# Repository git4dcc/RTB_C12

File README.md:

# RTB_C12

My homebrew RTB C12 Micro Booster implements a booster, DCC generator and Real-time Railcom detector. The booster is optimized for N-scale in respect to track voltage and current.

<details>
<summary>See also</summary>

- [RTB_C10 - Master](https://github.com/git4dcc/RTB_C10)
- [RTB_C11 - Power](https://github.com/git4dcc/RTB_C11)
- [RTB_C13 - Track Sensor](https://github.com/git4dcc/RTB_C13)
- [RTB_P15 - Base](https://github.com/git4dcc/RTB_P15)

</details>

<details>
<summary>User Guides</summary>

- User Guide - DE
- [User Guide - EN](https://rtb4dcc.de/rtb_user_guide_en/)

</details>

## Booster features
- **FDX**
  - FDX bus (2Mbps full duplex)
- **DCC protocol generator**
  - unlimited decoder stack depth
  - DCC bandwidth monitor
  - DCC-A protocol (incl. stretched start bit)
  - DCC-R protocol (incl. update of RTB decoder on main)
- **MDU protocol generator**
  - Zimo MDU ([Multi Decoder Update](https://github.com/ZIMO-Elektronik/MDU))
  - update of MS and MN decoder
  - can update multiple MN/MS decoder concurrently
- **DECUP protocol generator**
  - Zimo DECUP ([**Dec**oder **Up**date](https://github.com/ZIMO-Elektronik/DECUP))
  - update of MX decoder
- **Booster**
  - Software programmable output voltage (3..18V)
  - 1A continuous current (1.5A peak)
  - Current limiter
  - Short circuit detection
  - Configurable bridge dead time (170ns..3500ns)
  - DCC signal timing adjustable [micro sec granularity]
  - Railcom Cutout timing adjustable
  - Up to 500kHz fast signaling
  - Voltage and current measurement
- **Railcom Detector**
  - channel 1 / channel 2
  - detects unlimited number of decoder
  - Railcom polarity detection
  - Railcom timing capture for decoder analysis
- **Service Mode**
  - read/write DCC decoder in “service mode”
  - ACK current detector adjustable
- **Firmware update over the bus**

# Hardware
The PCB layout uses SMD footprints with 0.4mm pitch and mostly 0603 parts. Reflow soldering is recommended, but with some experience handsoldering is also possible.
Further, the PCB has been optimized for automated assembly (BOM and Position files as CSV).

## PCB
- 4-layer PCB, FR4, 1.6mm
- CPU: AVR64DB48
- H-Bridge: BD63573NUV
- Voltage: OPA521

## Kicad
[Schematic](doc/C12_schematic.pdf) | [Layout](doc/C12_layout.pdf) | [Gerber](gerber)

# Firmware
Filename structure: { **pcb** }{ **code** }{ **version** }.hex

Example: **C12F0001**.hex

|   | Description |
| --- | --- |
| **pcb** | Name of matching hardware (**C12**) |
| **code** | Type of code contained (**R**=rom, **B**=bootloader, **F**=flash, **U**=bld update, **P**=UPDI factory code) |
| **version** | Release version (**####**) |

[Firmware files](firmware)

## UPDI / Fuses
The fuse settings as well as the P-code (C12Pxxxx.hex) has to be installed by using UPDI.<br>

| Fuses Setting |
| --- |
||

# Images

# YouTube
See the C12 booster in action.<br><br>

This project is intended for hobby use only and is distributed in accordance with the Apache License 2.0 agreement.

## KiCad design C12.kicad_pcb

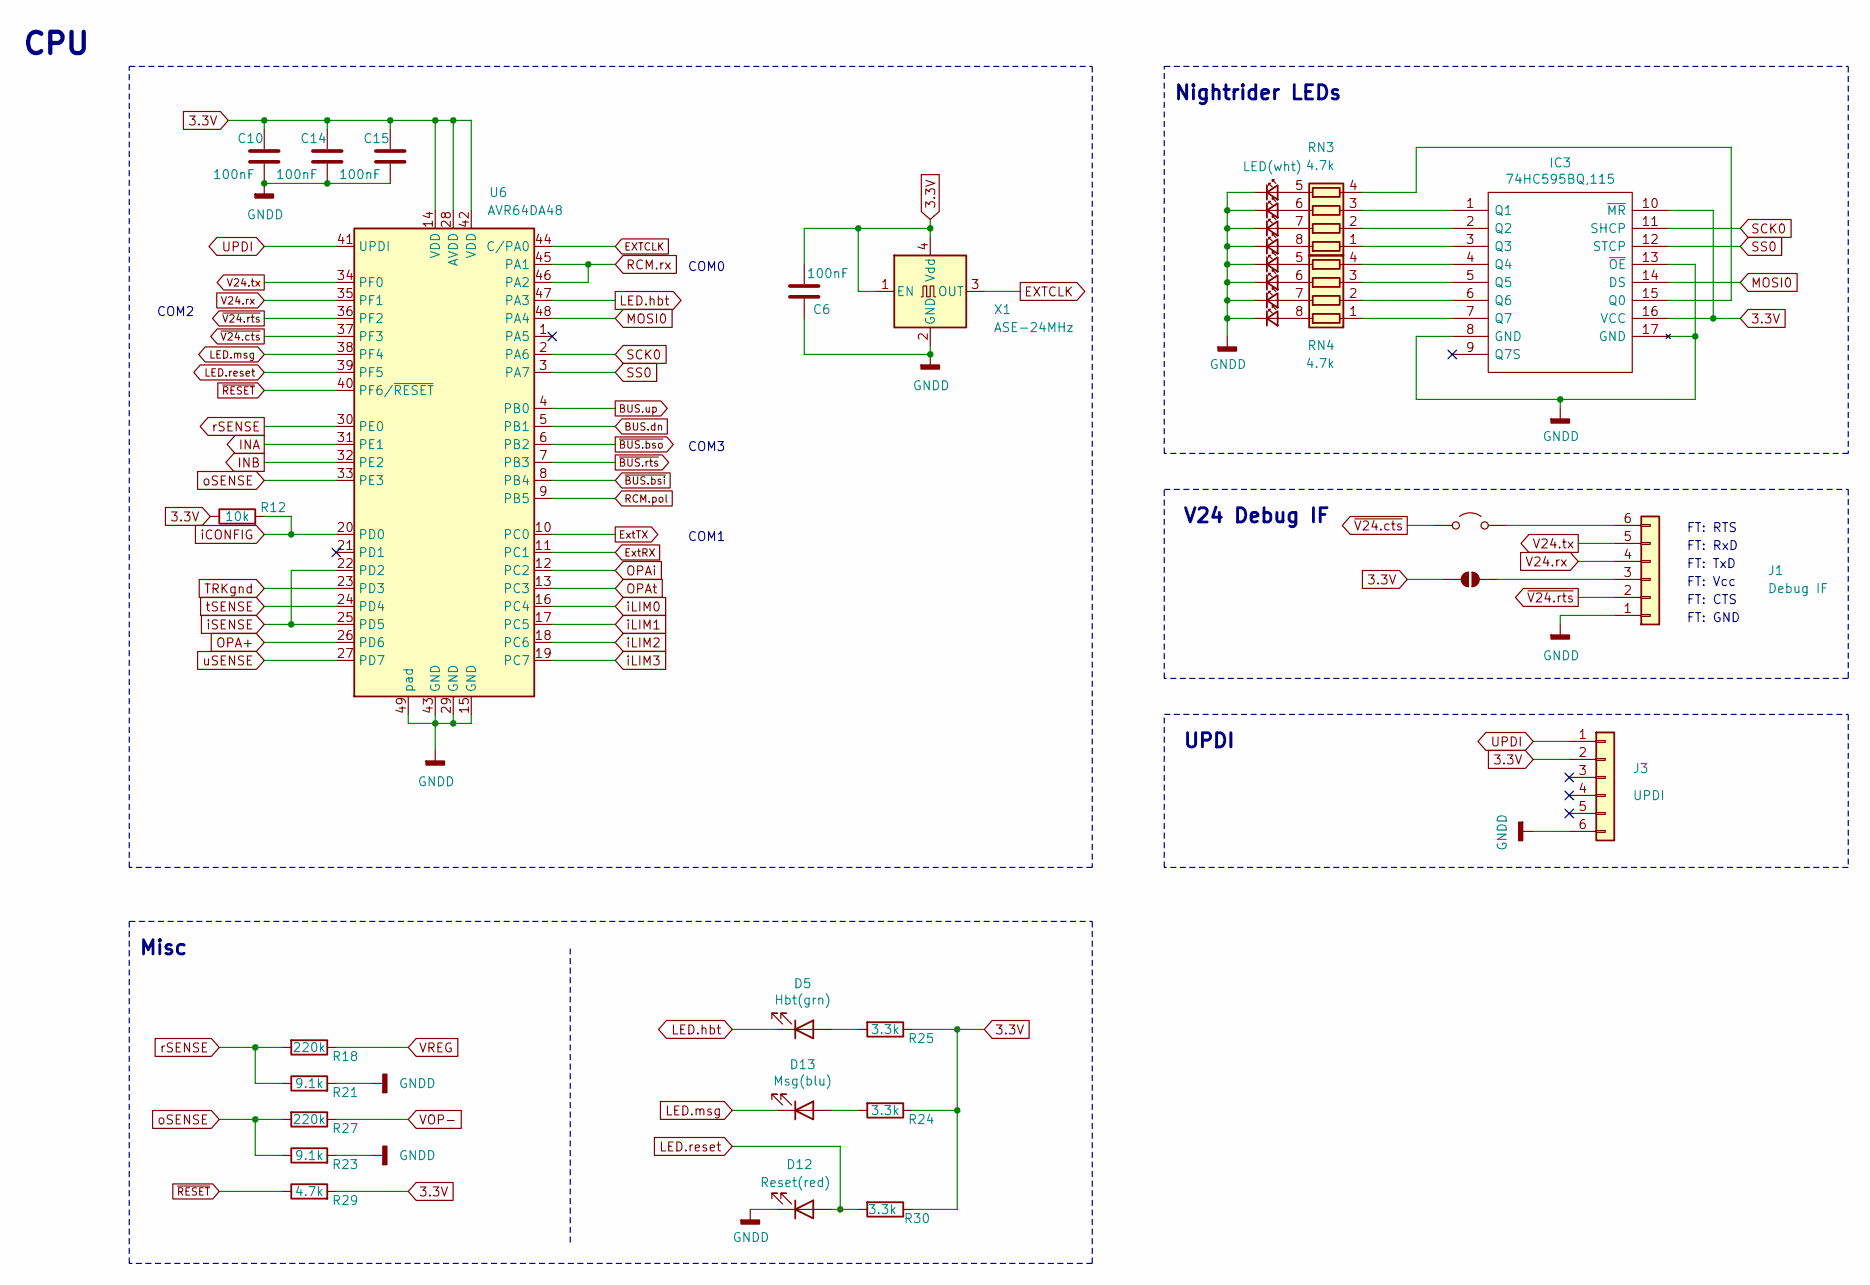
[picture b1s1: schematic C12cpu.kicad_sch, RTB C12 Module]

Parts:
C6, C10, C14, C15: 100nF; C_0402_1005Metric; LCSC Part # C307331
D5: Hbt(grn); LED_0603_1608Metric; LCSC Part # C84264
D12: Reset(red); LED_0603_1608Metric; LCSC Part # C2986060
D13: Msg(blu); LED_0603_1608Metric; LCSC Part # C434421
D14, D32, D33, D34, D35, D36, D37: LED_Small; LED_0603_1608Metric; LCSC Part # C2290
D38: LED(wht); LED_0603_1608Metric; LCSC Part # C2290
IC3: 74HC595BQ,115; DHVQFN-16-1EP_2.5x3.5mm_P0.5mm_EP1x2mm; LCSC Part # C547123
J1: Debug IF; PinHeader_1x06_P2.54mm_Vertical
J3: UPDI; PinHeader_2x03_P1.27mm_Vertical
JP1: Jumper_2_Open; PinHeader_1x02_P2.54mm_Vertical
JP2: SolderJumper_2_Open; SolderJumper-2_P1.3mm_Open_RoundedPad1.0x1.5mm
R12: 10k; R_0603_1608Metric; LCSC Part # C25804
R18, R27: 220k; R_0603_1608Metric; LCSC Part # C22961
R21, R23: 9.1k; R_0603_1608Metric; LCSC Part # C23260
R24, R25, R30: 3.3k; R_0603_1608Metric; LCSC Part # C22978
R29: 4.7k; R_0603_1608Metric; LCSC Part # C23162
RN3, RN4: 4.7k; R_Array_Convex_4x0603; LCSC Part # C1980
U6: AVR64DA48; QFN-48-1EP_6x6mm_P0.4mm_EP4.2x4.2mm; LCSC Part # C3227399
X1: ASE-24MHz; Oscillator_SMD_Abracon_ASE-4Pin_3.2x2.5mm; LCSC Part # C1987527

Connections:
3.3V: C6.1, C10.1, C14.1, C15.1, IC3.10 (~MR), IC3.16 (VCC), J3.2, JP2.1 (A), R12.1, R24.1, R25.1, R29.2, R30.1, U6.14 (VDD), U6.28 (AVDD), U6.42 (VDD), X1.1 (EN), X1.4 (Vdd); also elsewhere on the board
BUS.dn: U6.5 (PB1); also elsewhere on the board
BUS.up: U6.4 (PB0); also elsewhere on the board
EXTCLK: U6.44 (C/PA0), X1.3 (OUT)
ExtRX: U6.11 (PC1); also elsewhere on the board
ExtTX: U6.10 (PC0); also elsewhere on the board
GNDD: C6.2, C10.2, C14.2, C15.2, D12.1 (K), D14.1 (K), D32.1 (K), D33.1 (K), D34.1 (K), D35.1 (K), D36.1 (K), D37.1 (K), D38.1 (K), IC3.8 (GND), IC3.13 (~OE), IC3.17 (GND), J1.1, J3.6, R21.2, R23.2, U6.15 (GND), U6.29 (GND), U6.43 (GND), U6.49 (GND), X1.2 (GND); also elsewhere on the board
INA: U6.31 (PE1); also elsewhere on the board
INB: U6.32 (PE2); also elsewhere on the board
LED.hbt: D5.1 (K), U6.47 (PA3)
LED.msg: D13.1 (K), U6.38 (PF4)
LED.reset: D12.2 (A), R30.2, U6.39 (PF5)
MOSI0: IC3.14 (DS), U6.48 (PA4)
unnamed: D5.2 (A), R25.2
unnamed: D13.2 (A), R24.2
unnamed: D14.2 (A), RN4.8 (R1.2)
unnamed: D32.2 (A), RN4.7 (R2.2)
unnamed: D33.2 (A), RN4.6 (R3.2)
unnamed: D34.2 (A), RN4.5 (R4.2)
unnamed: D35.2 (A), RN3.8 (R1.2)
unnamed: D36.2 (A), RN3.7 (R2.2)
unnamed: D37.2 (A), RN3.6 (R3.2)
unnamed: D38.2 (A), RN3.5 (R4.2)
unnamed: IC3.15 (Q0), RN3.4 (R4.1)
unnamed: IC3.1 (Q1), RN3.3 (R3.1)
unnamed: IC3.2 (Q2), RN3.2 (R2.1)
unnamed: IC3.3 (Q3), RN3.1 (R1.1)
unnamed: IC3.4 (Q4), RN4.4 (R4.1)
unnamed: IC3.5 (Q5), RN4.3 (R3.1)
unnamed: IC3.6 (Q6), RN4.2 (R2.1)
unnamed: IC3.7 (Q7), RN4.1 (R1.1)
unnamed: J1.3, JP2.2 (B)
unnamed: J1.6, JP1.1 (A)
OPA+: U6.26 (PD6); also elsewhere on the board
OPAi: U6.12 (PC2); also elsewhere on the board
OPAt: U6.13 (PC3); also elsewhere on the board
RCM.pol: U6.9 (PB5); also elsewhere on the board
RCM.rx: U6.45 (PA1), U6.46 (PA2); also elsewhere on the board
SCK0: IC3.11 (SHCP), U6.2 (PA6)
SS0: IC3.12 (STCP), U6.3 (PA7)
TRKgnd: U6.23 (PD3); also elsewhere on the board
UPDI: J3.1, U6.41 (UPDI)
V24.rx: J1.4, U6.35 (PF1)
V24.tx: J1.5, U6.34 (PF0)
VOP-: R27.1; also elsewhere on the board
VREG: R18.1; also elsewhere on the board
iCONFIG: R12.2, U6.20 (PD0); also elsewhere on the board
iLIM0: U6.16 (PC4); also elsewhere on the board
iLIM1: U6.17 (PC5); also elsewhere on the board
iLIM2: U6.18 (PC6); also elsewhere on the board
iLIM3: U6.19 (PC7); also elsewhere on the board
iSENSE: U6.22 (PD2), U6.25 (PD5); also elsewhere on the board
oSENSE: R23.1, R27.2, U6.33 (PE3)
rSENSE: R18.2, R21.1, U6.30 (PE0)
tSENSE: U6.24 (PD4); also elsewhere on the board
uSENSE: U6.27 (PD7); also elsewhere on the board
~BUS.bsi: U6.8 (PB4); also elsewhere on the board
~BUS.bso: U6.6 (PB2); also elsewhere on the board
~BUS.rts: U6.7 (PB3); also elsewhere on the board
~RESET: R29.1, U6.40 (PF6/~RESET); also elsewhere on the board
~V24.cts: JP1.2 (B), U6.37 (PF3)
~V24.rts: J1.2, U6.36 (PF2)

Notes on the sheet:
FT: GND
Misc
COM0
COM1
UPDI
Nightrider LEDs
FT: RTS
FT: Vcc
FT: CTS
FT: RxD
COM2
COM3
FT: TxD
CPU
V24 Debug IF

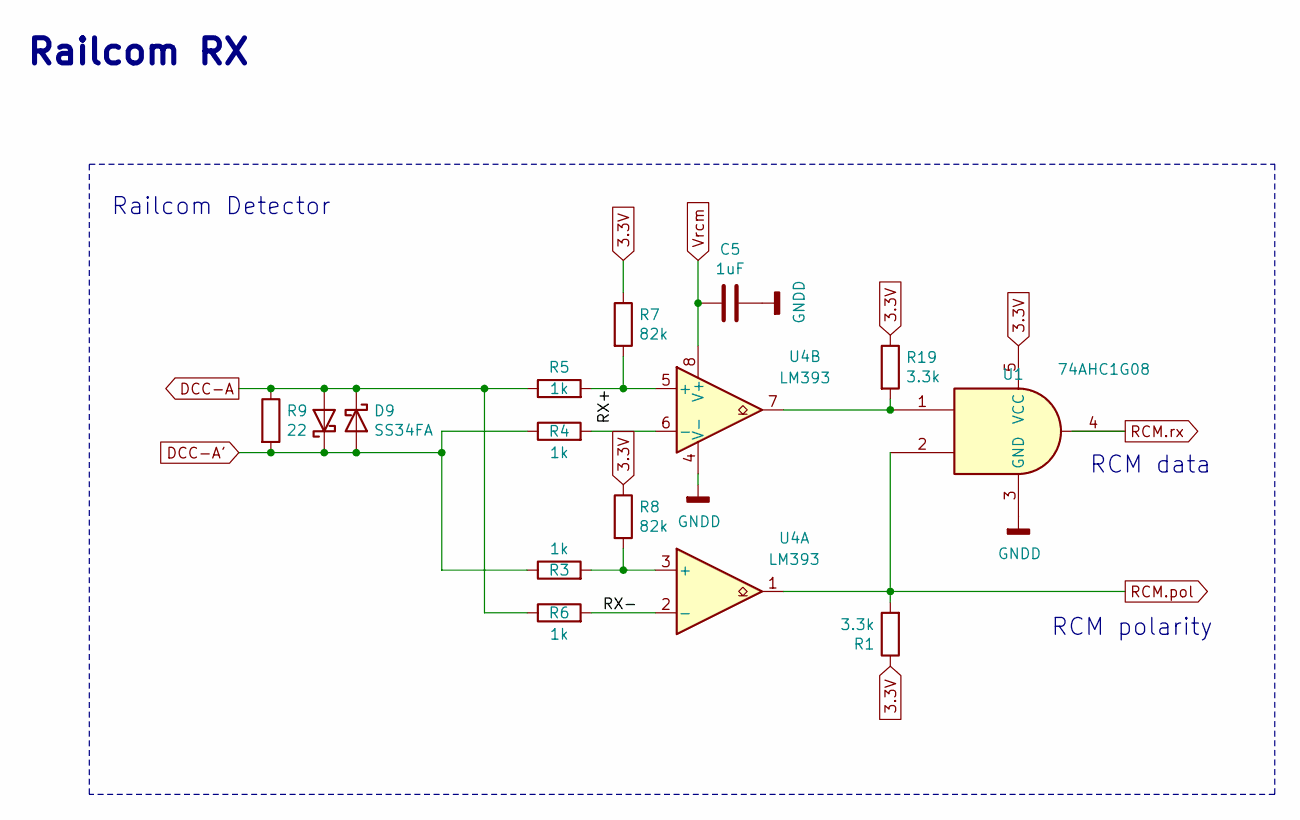
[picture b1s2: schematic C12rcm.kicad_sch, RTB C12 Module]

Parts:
C5: 1uF; C_0603_1608Metric; LCSC Part # C15849
D6, D9: SS34FA; D_SOD-123F; LCSC Part # C719833
R1, R19: 3.3k; R_0402_1005Metric; LCSC Part # C25890
R3, R4, R5, R6: 1k; R_0603_1608Metric; LCSC Part # C21190
R7, R8: 82k; R_0603_1608Metric; LCSC Part # C23254
R9: 22; R_0805_2012Metric; LCSC Part # C17561
U1: 74AHC1G08; SOT-353_SC-70-5; LCSC Part # C12490
U4: LM393; DFN-8-1EP_NG_2x2mm_Pitch0.5mm; LCSC Part # C2970927

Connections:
3.3V: R1.1, R7.1, R8.1, R19.1, U1.5 (VCC); also elsewhere on the board
/Railcom/RX+: R5.2, R7.2, U4.5 (+)
/Railcom/RX-: R6.2, U4.2 (-)
DCC-A: D6.2 (A), D9.1 (K), R5.1, R6.1, R9.1; also elsewhere on the board
DCC-A': D6.1 (K), D9.2 (A), R3.1, R4.1, R9.2; also elsewhere on the board
GNDD: C5.1, U1.3 (GND), U4.4 (V-); also elsewhere on the board
unnamed: R19.2, U1.1, U4.7
unnamed: R3.2, R8.2, U4.3 (+)
unnamed: R4.2, U4.6 (-)
RCM.pol: R1.2, U1.2, U4.1; also elsewhere on the board
RCM.rx: U1.4; also elsewhere on the board
Vrcm: C5.2, U4.8 (V+); also elsewhere on the board

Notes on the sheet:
Railcom Detector
Railcom RX
RCM polarity
RCM data

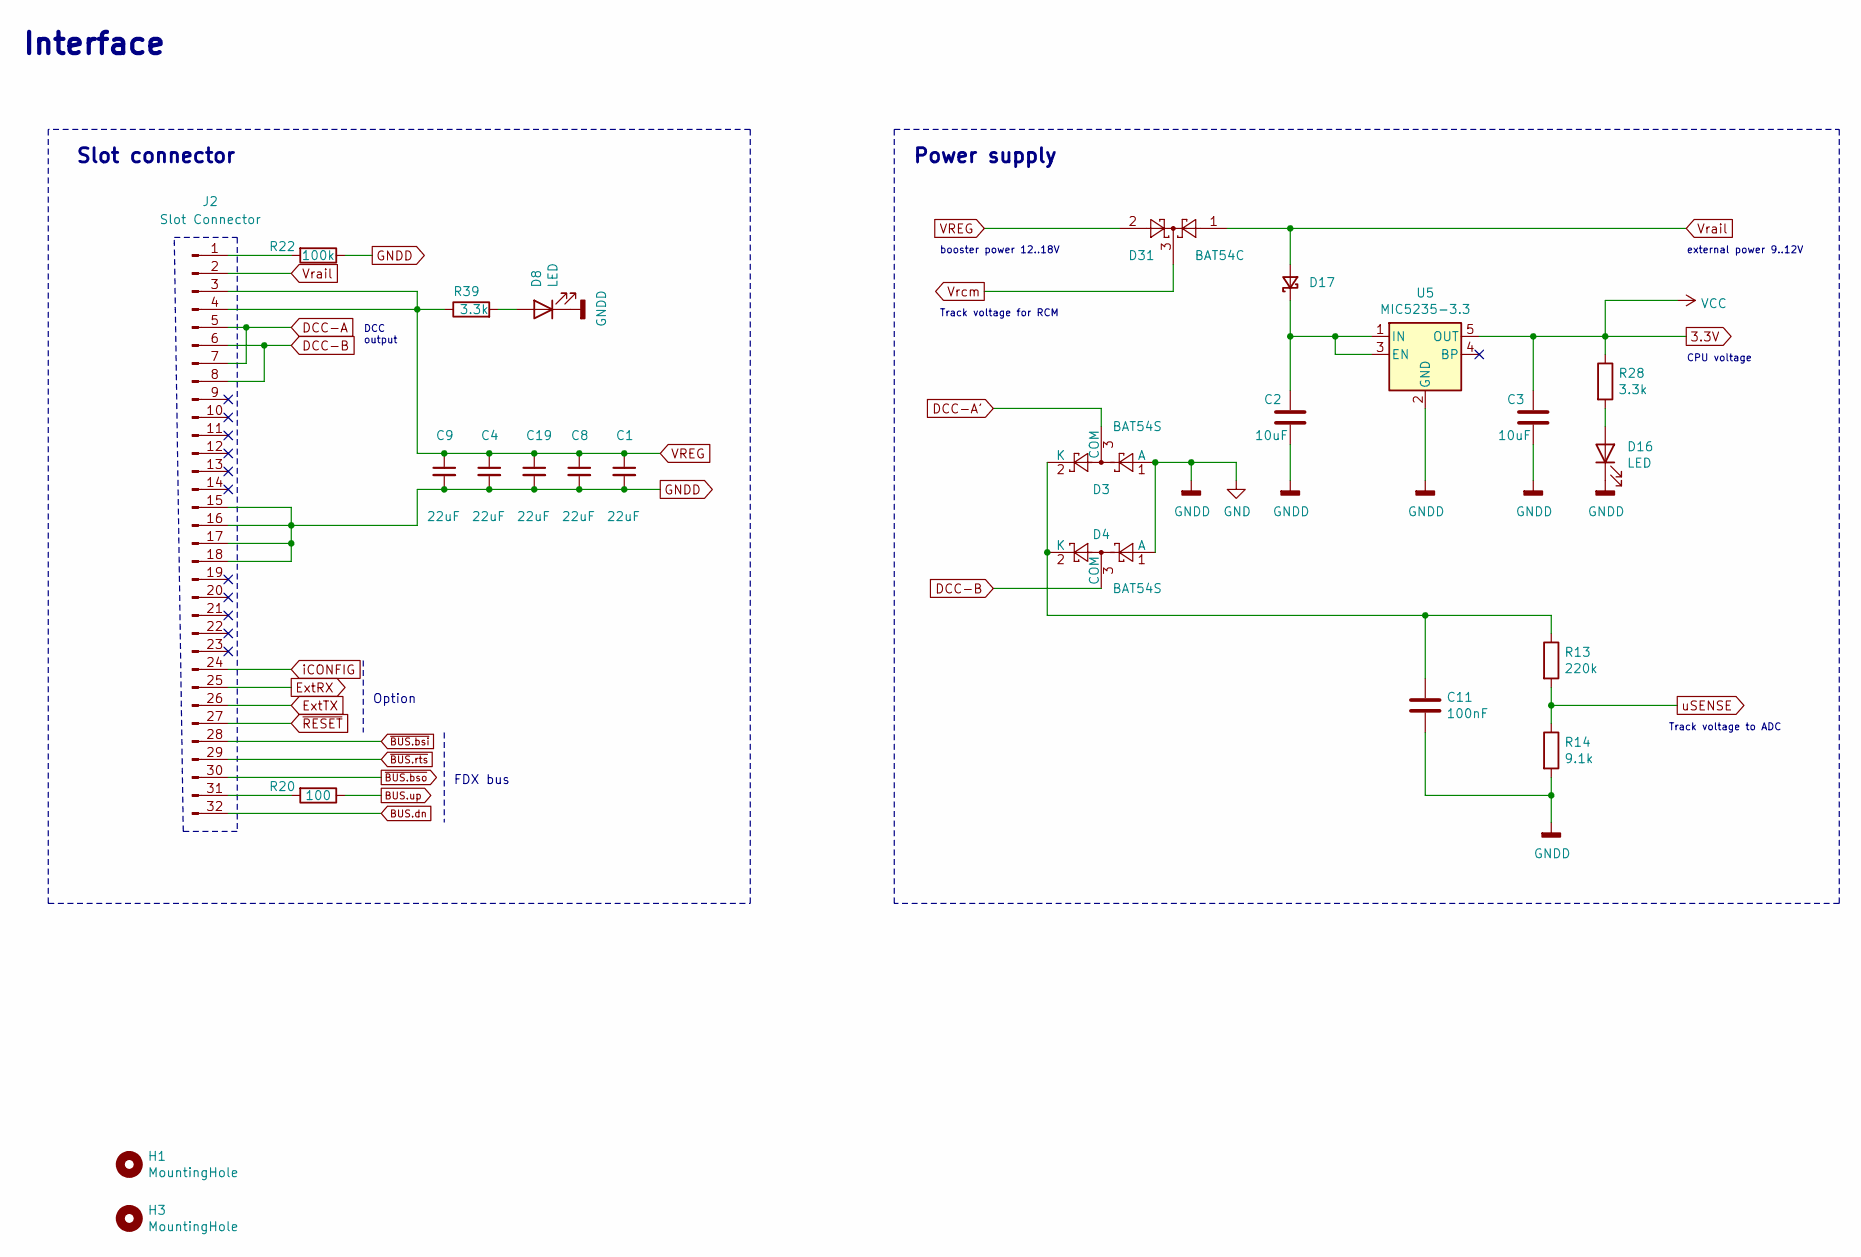
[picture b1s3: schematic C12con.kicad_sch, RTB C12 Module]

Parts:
C1, C4, C8, C9, C19: 22uF; C_1206_3216Metric; LCSC Part # C12891
C2, C3: 10uF; C_0805_2012Metric; LCSC Part # C440198
C11: 100nF; C_0603_1608Metric; LCSC Part # C14663
D3, D4: BAT54S; SOT-323_SC-70; LCSC Part # C549280
D8: LED; LED_0603_1608Metric; LCSC Part # C72038
D16: LED; LED_0603_1608Metric; LCSC Part # C84264
D17: D_Schottky_Small; D_MiniMELF; LCSC Part # C81181
D31: BAT54C; SOT-323_SC-70; LCSC Part # C82467
H1, H3: MountingHole; MountingHole_3.2mm_M3_ISO7380_Pad
J2: Slot Connector; PinHeader_1x32_P2.54mm_Vertical
R13: 220k; R_0603_1608Metric; LCSC Part # C22961
R14: 9.1k; R_0603_1608Metric; LCSC Part # C23260
R20: 100; R_0603_1608Metric; LCSC Part # C22775
R22: 100k; R_0603_1608Metric; LCSC Part # C25803
R28, R39: 3.3k; R_0603_1608Metric; LCSC Part # C22978
U5: MIC5235-3.3; SOT-23-5; LCSC Part # C89886

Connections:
3.3V: C3.1, R28.1, U5.5 (OUT); also elsewhere on the board
BUS.dn: J2.32; also elsewhere on the board
BUS.up: R20.1; also elsewhere on the board
DCC-A: J2.5, J2.7; also elsewhere on the board
DCC-A': D3.3 (COM); also elsewhere on the board
DCC-B: D4.3 (COM), J2.6, J2.8; also elsewhere on the board
ExtRX: J2.25; also elsewhere on the board
ExtTX: J2.26; also elsewhere on the board
GNDD: C1.2, C2.2, C3.2, C4.2, C8.2, C9.2, C11.2, C19.2, D3.1 (A), D4.1 (A), D8.1 (K), D16.1 (K), J2.15, J2.16, J2.17, J2.18, R14.2, R22.1, U5.2 (GND); also elsewhere on the board
unnamed: C11.1, D3.2 (K), D4.2 (K), R13.1
unnamed: D8.2 (A), R39.2
unnamed: D16.2 (A), R28.2
unnamed: C2.1, D17.1 (K), U5.1 (IN), U5.3 (EN)
unnamed: J2.1, R22.2
unnamed: J2.31, R20.2
VREG: C1.1, C4.1, C8.1, C9.1, C19.1, D31.2, J2.3, J2.4, R39.1; also elsewhere on the board
Vrail: D17.2 (A), D31.1, J2.2
Vrcm: D31.3; also elsewhere on the board
iCONFIG: J2.24; also elsewhere on the board
uSENSE: R13.2, R14.1; also elsewhere on the board
~BUS.bsi: J2.28; also elsewhere on the board
~BUS.bso: J2.30; also elsewhere on the board
~BUS.rts: J2.29; also elsewhere on the board
~RESET: J2.27; also elsewhere on the board

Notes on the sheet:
booster power 12..18V
FDX bus
Track voltage for RCM
Slot connector
Interface
CPU voltage
Track voltage to ADC
Power supply
DCC output
Option
external power 9..12V

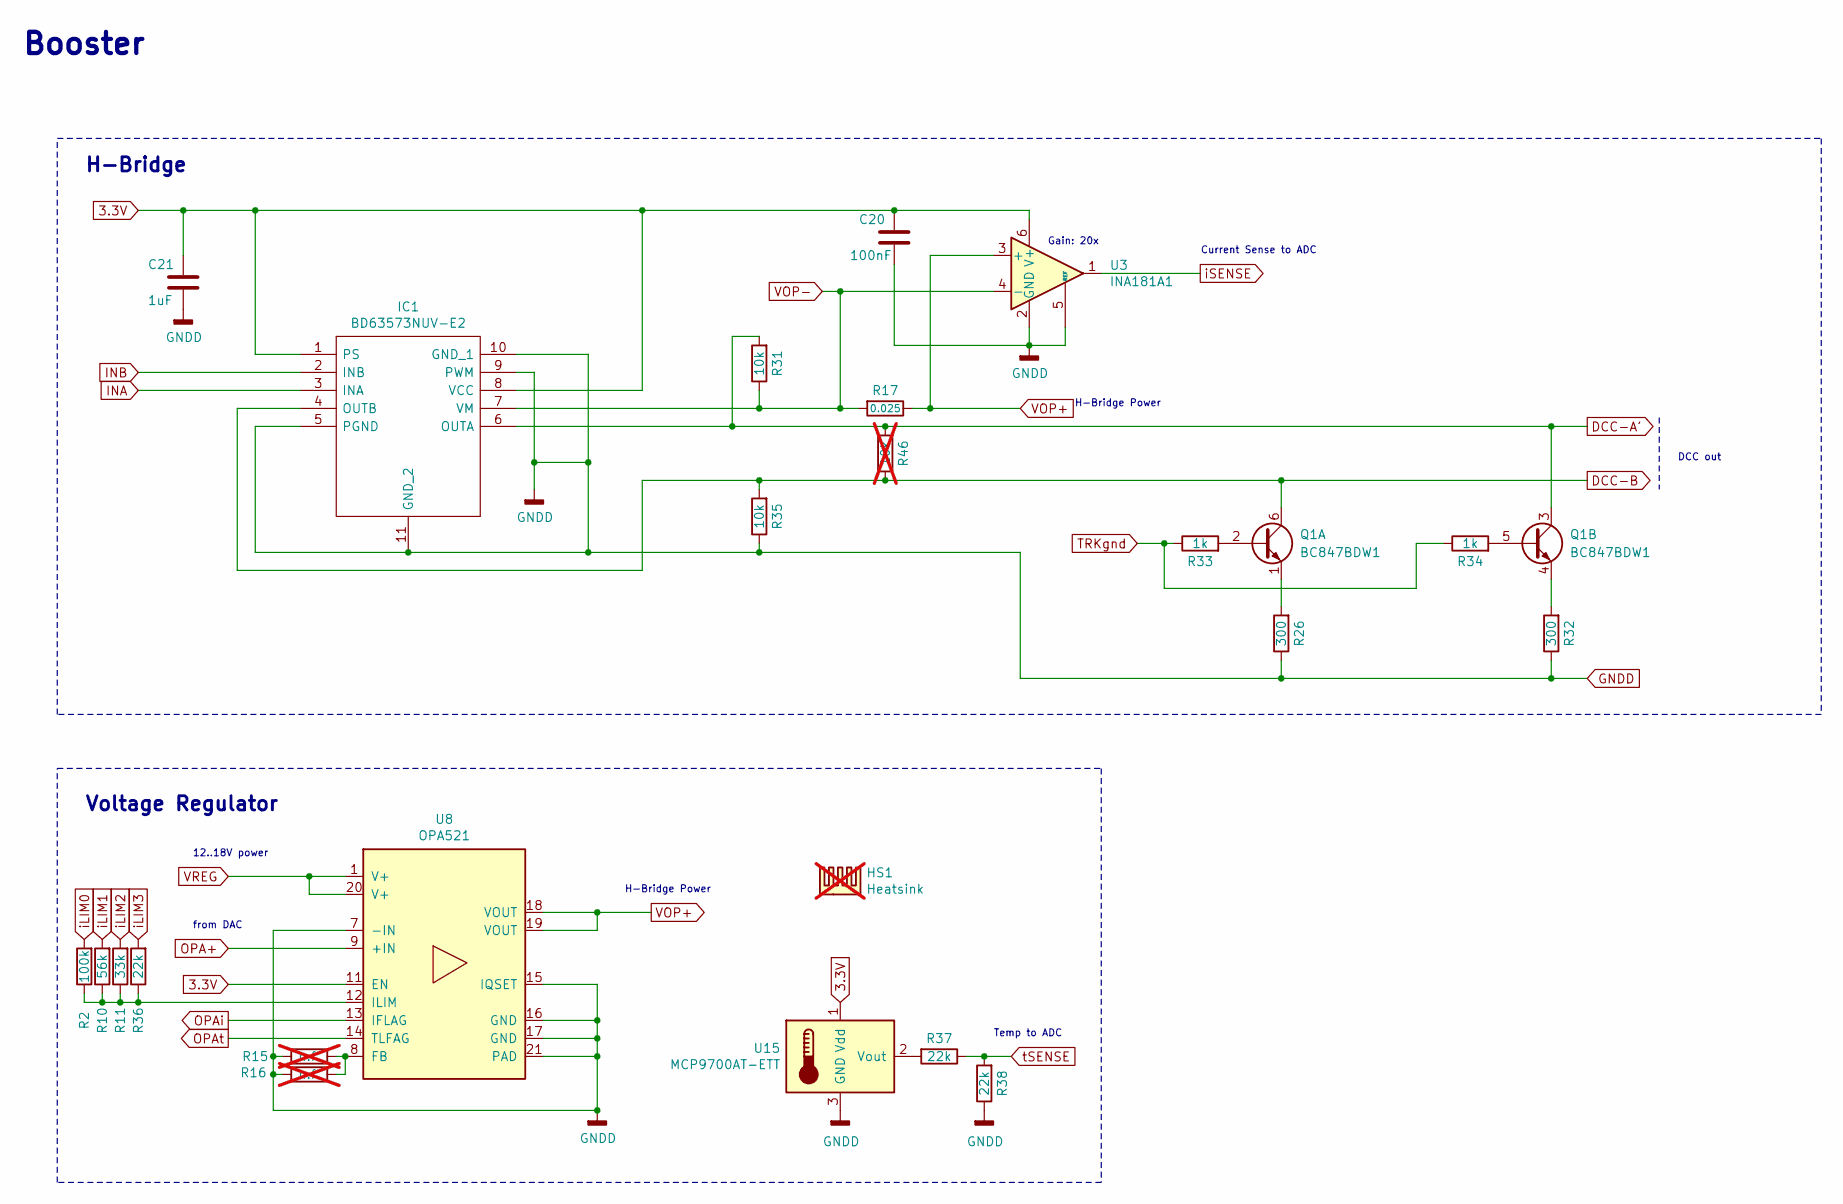
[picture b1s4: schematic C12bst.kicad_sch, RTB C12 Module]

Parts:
C20: 100nF; C_0603_1608Metric; LCSC Part # C14663
C21: 1uF; C_0603_1608Metric; LCSC Part # C15849
HS1: Heatsink; Heatsink_AAVID_573300D00010G_TO-263; not fitted
IC1: BD63573NUV-E2; VSON-10-1EP_3x3mm_P0.5mm_EP1.2x2mm; LCSC Part # C2150564
Q1: BC847BDW1; SOT-363_SC-70-6; LCSC Part # C82368
R2: 100k; R_0603_1608Metric; LCSC Part # C25803
R10: 56k; R_0603_1608Metric; LCSC Part # C23206
R11: 33k; R_0603_1608Metric; LCSC Part # C4216
R15, R16: n.f.; R_0603_1608Metric; not fitted
R17: 0.025; R_2010_5025Metric; LCSC Part # C22470461
R26, R32: 300; L_1206_3216Metric; LCSC Part # C17887
R31: 10k; R_0805_2012Metric; LCSC Part # C17414
R33, R34: 1k; R_0603_1608Metric; LCSC Part # C21190
R35: 10k; R_0603_1608Metric; LCSC Part # C25804
R36, R37, R38: 22k; R_0603_1608Metric; LCSC Part # C31850
R46: 10k; R_0603_1608Metric; LCSC Part # C25804; not fitted
U3: INA181A1; SOT-23-6; LCSC Part # C2058943
U8: OPA521; QFN-20-1EP_5x5mm_P0.65mm_EP3.35x3.35mm; LCSC Part # C2058423
U15: MCP9700AT-ETT; SOT-23; LCSC Part # C127949

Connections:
3.3V: C20.1, C21.1, IC1.1 (PS), IC1.8 (VCC), U3.6 (V+), U8.11 (EN), U15.1 (Vdd); also elsewhere on the board
DCC-A': IC1.6 (OUTA), Q1.3 (C2), R31.2, R46.2; also elsewhere on the board
DCC-B: IC1.4 (OUTB), Q1.6 (C1), R35.2, R46.1; also elsewhere on the board
GNDD: C20.2, C21.2, IC1.5 (PGND), IC1.9 (PWM), IC1.10 (GND_1), IC1.11 (GND_2), R15.2, R16.2, R26.1, R32.1, R35.1, R38.1, U3.2 (GND), U3.5 (REF), U8.7 (-IN), U8.15 (IQSET), U8.16 (GND), U8.17 (GND), U8.21 (PAD), U15.3 (GND); also elsewhere on the board
INA: IC1.3 (INA); also elsewhere on the board
INB: IC1.2 (INB); also elsewhere on the board
unnamed: Q1.2 (B1), R33.2
unnamed: Q1.1 (E1), R26.2
unnamed: Q1.5 (B2), R34.2
unnamed: Q1.4 (E2), R32.2
unnamed: R15.1, R16.1, U8.8 (FB)
unnamed: R2.1, R10.1, R11.1, R36.1, U8.12 (ILIM)
unnamed: R37.2, U15.2 (Vout)
OPA+: U8.9 (+IN); also elsewhere on the board
OPAi: U8.13 (IFLAG); also elsewhere on the board
OPAt: U8.14 (TLFAG); also elsewhere on the board
TRKgnd: R33.1, R34.1; also elsewhere on the board
VOP+: R17.1, U3.3 (+), U8.18 (VOUT), U8.19 (VOUT)
VOP-: IC1.7 (VM), R17.2, R31.1, U3.4 (-); also elsewhere on the board
VREG: U8.1 (V+), U8.20 (V+); also elsewhere on the board
iLIM0: R2.2; also elsewhere on the board
iLIM1: R10.2; also elsewhere on the board
iLIM2: R11.2; also elsewhere on the board
iLIM3: R36.2; also elsewhere on the board
iSENSE: U3.1; also elsewhere on the board
tSENSE: R37.1, R38.2; also elsewhere on the board

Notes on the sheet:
Current Sense to ADC
Voltage Regulator
H-Bridge
Temp to ADC
H-Bridge Power
DCC out
12..18V power
Booster
Gain: 20x
from DAC

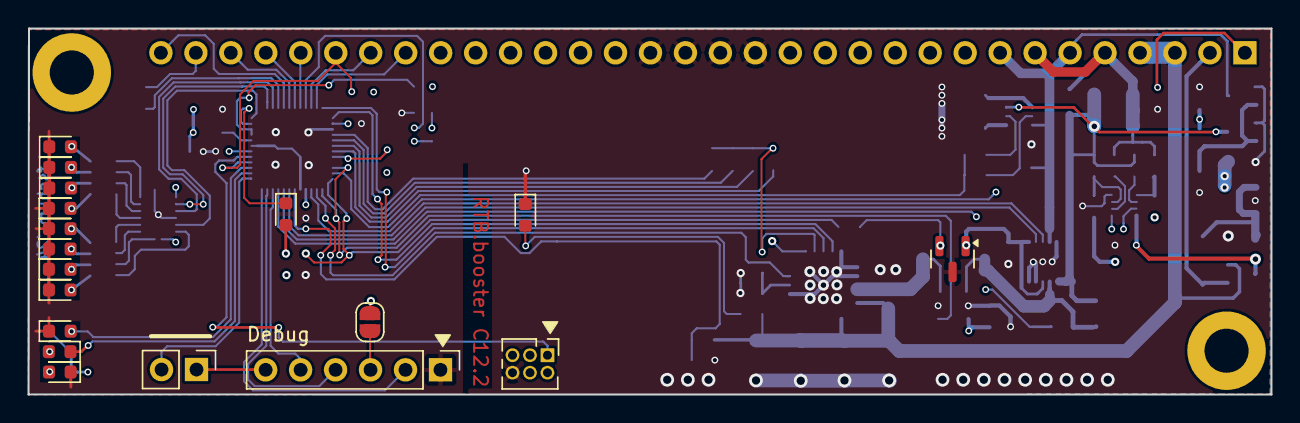
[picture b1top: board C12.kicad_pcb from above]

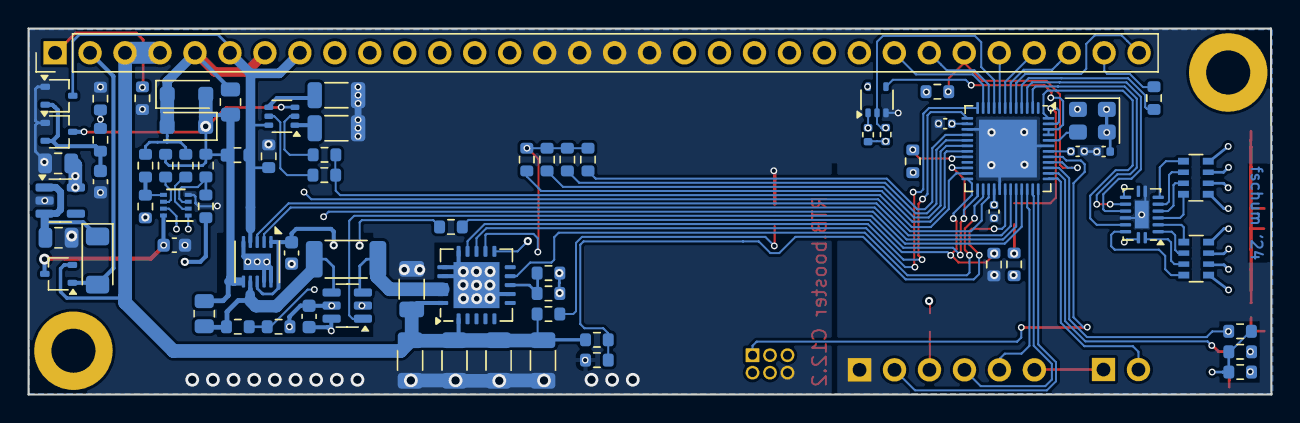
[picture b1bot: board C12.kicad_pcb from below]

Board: 4 copper layers, 90.3 x 26.6 mm, 94 parts (76 on the bottom side), 86 nets.

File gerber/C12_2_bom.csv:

Designator,Footprint,Quantity,Value,LCSC Part #
"C1, C19, C4, C8, C9",1206,5,22uF,C12891
"C10, C14, C15, C6",0402,4,100nF,C307331
"C11, C20",0603,2,100nF,C14663
"C2, C3",0805,2,10uF,C440198
"C21, C5",0603,2,1uF,C15849
D12,0603,1,Reset(red),C2986060
D13,0603,1,Msg(blu),C434421
"D14, D32, D33, D34, D35, D36, D37",0603,7,LED_Small,C2290
D16,0603,1,LED,C84264
D17,D_MiniMELF,1,D_Schottky_Small,C81181
"D3, D4",SOT-323_SC-70,2,BAT54S,C549280
D31,SOT-323_SC-70,1,BAT54C,C82467
D38,0603,1,LED(wht),C2290
D5,0603,1,Hbt(grn),C84264
"D6, D9",D_SOD-123F,2,SS34FA,C719833
D8,0603,1,LED,C72038
"H1, H3",MountingHole_3.2mm_M3_ISO7380_Pad,2,MountingHole,
IC1,VSON-10-1EP_3x3mm_P0.5mm_EP1.2x2mm,1,BD63573NUV-E2,C2150564
IC3,DHVQFN-16-1EP_2.5x3.5mm_P0.5mm_EP1x2mm,1,"74HC595BQ,115",C547123
J1,PinHeader_1x06_P2.54mm_Vertical,1,Debug IF,
J2,PinHeader_1x32_P2.54mm_Vertical,1,Slot Connector,
J3,PinHeader_2x03_P1.27mm_Vertical,1,UPDI,
JP1,PinHeader_1x02_P2.54mm_Vertical,1,Jumper_2_Open,
JP2,SolderJumper-2_P1.3mm_Open_RoundedPad1.0x1.5mm,1,SolderJumper_2_Open,
Q1,SOT-363_SC-70-6,1,BC847BDW1,C82368
"R1, R19",0402,2,3.3k,C25890
R10,0603,1,56k,C23206
R11,0603,1,33k,C4216
"R12, R35",0603,2,10k,C25804
"R13, R18, R27",0603,3,220k,C22961
"R14, R21, R23",0603,3,9.1k,C23260
R17,2010,1,0.025,C22470461
"R2, R22",0603,2,100k,C25803
R20,0603,1,100,C22775
"R24, R25, R28, R30, R39",0603,5,3.3k,C22978
"R26, R32",1206,2,300,C17887
R29,0603,1,4.7k,C23162
"R3, R33, R34, R4, R5, R6",0603,6,1k,C21190
R31,0805,1,10k,C17414
"R36, R37, R38",0603,3,22k,C31850
"R7, R8",0603,2,82k,C23254
R9,0805,1,22,C17561
"RN3, RN4",R_Array_Convex_4x0603,2,4.7k,C1980
U1,SOT-353_SC-70-5,1,74AHC1G08,C12490
U15,SOT-23,1,MCP9700AT-ETT,C127949
U3,SOT-23-6,1,INA181A1,C2058943
U4,DFN-8-1EP_NG_2x2mm_Pitch0.5mm,1,LM393,C2970927
U5,SOT-23-5,1,MIC5235-3.3,C89886
U6,QFN-48-1EP_6x6mm_P0.4mm_EP4.2x4.2mm,1,AVR64DA48,C3227399
U8,QFN-20-1EP_5x5mm_P0.65mm_EP3.35x3.35mm,1,OPA521,C2058423
X1,Oscillator_SMD_Abracon_ASE-4Pin_3.2x2.5mm,1,ASE-24MHz,C1987527

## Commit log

2025-08-07 initial
2025-09-02 mod: optimized for PCB assembly
2025-09-25 upgrade to Kicad 9
2025-10-02 add: external ILM detection
2025-11-18 mod: refactoring
2025-11-18 add: fuses document
2025-11-18 Add UPDI / Fuses section to README
    Added UPDI and fuse settings section to README.
2025-12-10 Document Zimo MDU generator in README
    Added Zimo MDU generator feature to README.
2025-12-10 Update MDU generator description in README
2025-12-15 add: Zimo MDU protocol for MN/MS decoder updates
2026-01-17 Update README with protocol descriptions and links
